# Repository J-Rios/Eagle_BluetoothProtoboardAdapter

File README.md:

# Eagle_BluetoothProtoboardAdapter
Bluetooth modules breakout adapter to make it breadboard friendly.
[See Image of the board](Image.png).

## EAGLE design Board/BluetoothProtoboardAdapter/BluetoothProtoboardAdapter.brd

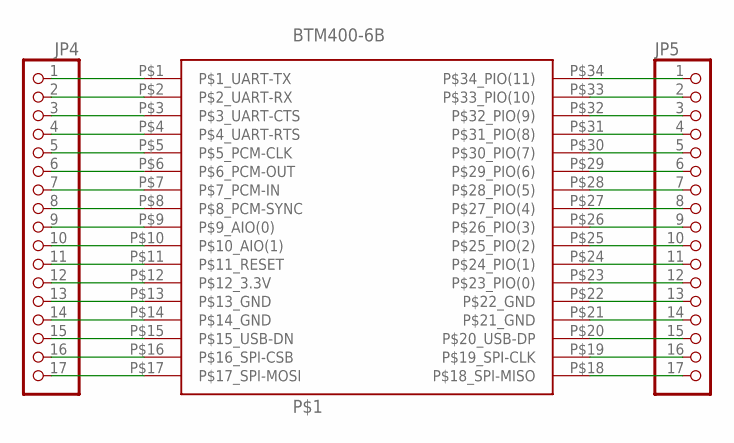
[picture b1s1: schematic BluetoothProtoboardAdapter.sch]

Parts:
JP4, JP5: PINHD-1X17; 1X17
P$1: BTM400-6B; BTM400

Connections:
unnamed: JP4.1, P$1.P$1 (P$1_UART-TX)
unnamed: JP4.2, P$1.P$2 (P$2_UART-RX)
unnamed: JP4.3, P$1.P$3 (P$3_UART-CTS)
unnamed: JP4.4, P$1.P$4 (P$4_UART-RTS)
unnamed: JP4.5, P$1.P$5 (P$5_PCM-CLK)
unnamed: JP4.6, P$1.P$6 (P$6_PCM-OUT)
unnamed: JP4.7, P$1.P$7 (P$7_PCM-IN)
unnamed: JP4.8, P$1.P$8 (P$8_PCM-SYNC)
unnamed: JP4.9, P$1.P$9 (P$9_AIO(0))
unnamed: JP4.10, P$1.P$10 (P$10_AIO(1))
unnamed: JP4.11, P$1.P$11 (P$11_RESET)
unnamed: JP4.12, P$1.P$12 (P$12_3.3V)
unnamed: JP4.15, P$1.P$15 (P$15_USB-DN)
unnamed: JP4.16, P$1.P$16 (P$16_SPI-CSB)
unnamed: JP5.17, P$1.P$18 (P$18_SPI-MISO)
unnamed: JP5.13, P$1.P$22 (P$22_GND)
unnamed: JP4.17, P$1.P$17 (P$17_SPI-MOSI)
unnamed: JP5.1, P$1.P$34 (P$34_PIO(11))
unnamed: JP5.2, P$1.P$33 (P$33_PIO(10))
unnamed: JP5.3, P$1.P$32 (P$32_PIO(9))
unnamed: JP5.4, P$1.P$31 (P$31_PIO(8))
unnamed: JP5.5, P$1.P$30 (P$30_PIO(7))
unnamed: JP5.6, P$1.P$29 (P$29_PIO(6))
unnamed: JP5.7, P$1.P$28 (P$28_PIO(5))
unnamed: JP5.8, P$1.P$27 (P$27_PIO(4))
unnamed: JP5.9, P$1.P$26 (P$26_PIO(3))
unnamed: JP5.10, P$1.P$25 (P$25_PIO(2))
unnamed: JP5.12, P$1.P$23 (P$23_PIO(0))
unnamed: JP5.14, P$1.P$21 (P$21_GND)
unnamed: JP5.15, P$1.P$20 (P$20_USB-DP)
unnamed: JP5.16, P$1.P$19 (P$19_SPI-CLK)
unnamed: JP5.11, P$1.P$24 (P$24_PIO(1))
unnamed: JP4.13, P$1.P$13 (P$13_GND)
unnamed: JP4.14, P$1.P$14 (P$14_GND)

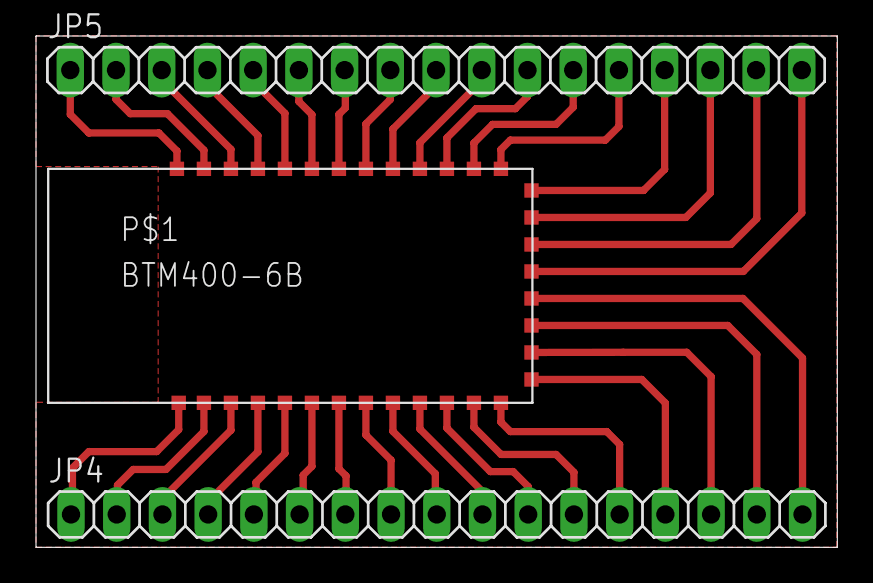
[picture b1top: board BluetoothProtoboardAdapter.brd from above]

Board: 2 copper layers, 44.5 x 28.4 mm, 3 parts (0 on the bottom side), 34 nets.

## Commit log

2015-05-02 Board
    Eagle board files added
2015-05-02 Board
    Change name of the project
2015-05-04 Image
    Image added
